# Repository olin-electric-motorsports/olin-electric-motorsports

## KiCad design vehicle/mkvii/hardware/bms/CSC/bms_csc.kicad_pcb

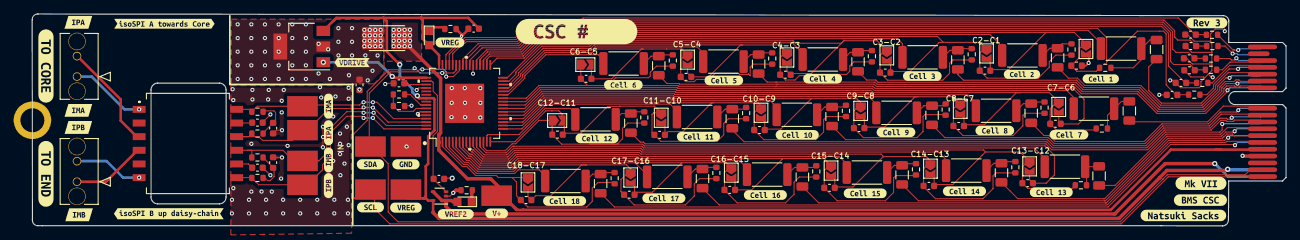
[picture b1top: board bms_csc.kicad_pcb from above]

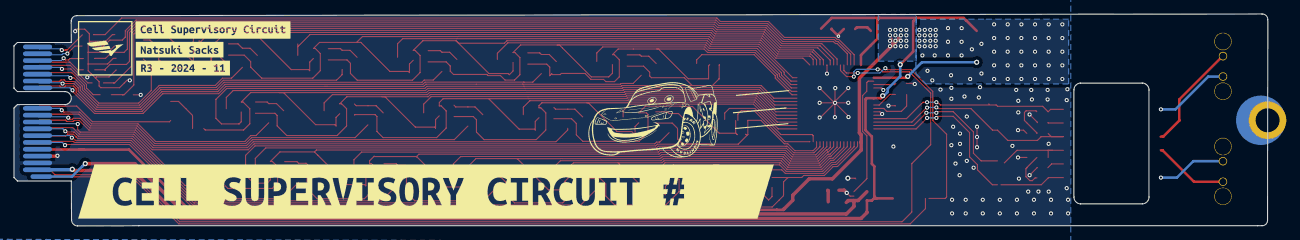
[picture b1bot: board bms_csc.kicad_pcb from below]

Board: 2 copper layers, 183.7 x 31.1 mm, 185 parts (4 on the bottom side), 110 nets.

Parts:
C1, C2, C3: C_1uF; C_0603
C4: C_0.1uF; C_0603
C5, C6, C7, C8, C9, C10, C11, C12, C13, C14, C15, C16, C17, C18, C19, C20, C21, C22, C23, C24, C25, C26, C27, C28, C29, C30, C31, C32: C_10nF; C_0603
D1, D2: LED_WHITE; CHIPLED_0805
F1, F2, F3, F4, F5, F6, F7, F8, F9, F10, F11, F12, F13, F14, F15, F16, F17, F18: 200mA_Fuse; Fuse_1206_3216Metric
H1: CONN_MountingHole; PCIe_Mount
J1, J2: 436500220; CONN_436500220
J8: CONN_pcie_x1; pcie_x1
JP1, JP2, JP3, JP4, JP5, JP6, JP7, JP8, JP9, JP10, JP11, JP12, JP13, JP14, JP15, JP16, JP17, JP18: SolderJumper_2_Open; SolderJumper-2_P1.3mm_Open_TrianglePad1.0x1.5mm
Q1: NSS1C201MZ4; SOT-223
R3: R_100; R_2512_OEM
R4, R5, R6, R7: R_60.4; R_0603
R8: 80; R_0603
R9, R10, R12, R51, R52, R53: R_100; R_0603
R11: 422; R_0603
R13, R14: R_1K; R_0603
R15, R17, R19, R21, R23, R25, R27, R29, R31, R33, R35, R37, R39, R41, R43, R45, R47, R49: 22R-1W; R_2512_6332Metric
R16, R18, R20, R22, R24, R26, R28, R30, R32, R34, R36, R38, R40, R42, R44, R46, R48, R50: 10R; R_0603
T1: HM2112ZNLT
TP1, TP2, TP3, TP4, TP19, TP20: TP_SMD; Test_Point_SMD
TP9, TP10, TP11: TP_1mm; Test_Point_SMD
U1: ADBMS1818; LQFP-64-1EP_12x12_P0.5
U2: MCP6001T-I-LT; SOT-353_SC-70-5
kibuzzard-63B4D82F: G***; kibuzzard-63B4D82F
kibuzzard-63B4D834: G***; kibuzzard-63B4D834
kibuzzard-63B4E58E: G***; kibuzzard-63B4E58E
kibuzzard-63B4E59A: G***; kibuzzard-63B4E59A
kibuzzard-63B4E581: G***; kibuzzard-63B4E581
kibuzzard-63B4E593: G***; kibuzzard-63B4E593
kibuzzard-63B4EB9B: G***; kibuzzard-63B4EB9B
kibuzzard-63B4EBA9: G***; kibuzzard-63B4EBA9
kibuzzard-63B4EBAD: G***; kibuzzard-63B4EBAD
kibuzzard-63B4EBB3: G***; kibuzzard-63B4EBB3
kibuzzard-63B4EBB8: G***; kibuzzard-63B4EBB8
kibuzzard-63B4EBF9: G***; kibuzzard-63B4EBF9
kibuzzard-63B4EC1B: G***; kibuzzard-63B4EC1B
kibuzzard-63B4EC4E: G***; kibuzzard-63B4EC4E
kibuzzard-63B4EC5B: G***; kibuzzard-63B4EC5B
kibuzzard-63B4EC6B: G***; kibuzzard-63B4EC6B
kibuzzard-63B4EC7A: G***; kibuzzard-63B4EC7A
kibuzzard-63B4EC20: G***; kibuzzard-63B4EC20
kibuzzard-63B4EC53: G***; kibuzzard-63B4EC53
kibuzzard-63B4EC66: G***; kibuzzard-63B4EC66
kibuzzard-63B4EC74: G***; kibuzzard-63B4EC74
kibuzzard-63B4EC80: G***; kibuzzard-63B4EC80
kibuzzard-63B4ED2A: G***; kibuzzard-63B4ED2A
kibuzzard-63B4ED25: G***; kibuzzard-63B4ED25
kibuzzard-63B4ED94: G***; kibuzzard-63B4ED94
kibuzzard-63BF4D5E: G***; kibuzzard-63BF4D5E
kibuzzard-672FCAF7: G***; kibuzzard-672FCAF7
kibuzzard-672FCF9D: G***; kibuzzard-672FCF9D
kibuzzard-673A717E: G***; kibuzzard-673A717E
kibuzzard-673A718C: G***; kibuzzard-673A718C
kibuzzard-673A725C: G***; kibuzzard-673A725C
kibuzzard-673A7082: G***; kibuzzard-673A7082
kibuzzard-673A7176: G***; kibuzzard-673A7176
kibuzzard-673A7184: G***; kibuzzard-673A7184
kibuzzard-673AA1F5: G***; kibuzzard-673AA1F5
kibuzzard-673AA1FB: G***; kibuzzard-673AA1FB
kibuzzard-673AA20C: G***; kibuzzard-673AA20C
kibuzzard-673AA233: G***; kibuzzard-673AA233
kibuzzard-6736A7FC: G***; kibuzzard-6736A7FC
kibuzzard-6736A805: G***; kibuzzard-6736A805
kibuzzard-6736A828: G***; kibuzzard-6736A828
kibuzzard-6736A857: G***; kibuzzard-6736A857
kibuzzard-6736A863: G***; kibuzzard-6736A863
kibuzzard-67399BB2: G***; kibuzzard-67399BB2
kibuzzard-673993C6: G***; kibuzzard-673993C6
kibuzzard-673998AC: G***; kibuzzard-673998AC
kibuzzard-6731260F: G***; kibuzzard-6731260F

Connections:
/C1: C25.2, C26.1, JP17.2 (B), JP18.1 (A), R50.2, U1.36 (C1)
/C2: C24.2, C25.1, JP16.2 (B), JP17.1 (A), R48.2, U1.34 (C2)
/C3: C23.2, C24.1, JP15.2 (B), JP16.1 (A), R46.2, U1.32 (C3)
/C4: C22.2, C23.1, JP14.2 (B), JP15.1 (A), R44.2, U1.30 (C4)
/C5: C21.2, C22.1, JP13.2 (B), JP14.1 (A), R42.2, U1.28 (C5)
/C6: C20.2, C21.1, JP12.2 (B), JP13.1 (A), R40.2, U1.26 (C6)
/C7: C19.2, C20.1, JP11.2 (B), JP12.1 (A), R38.2, U1.24 (C7)
/C8: C18.2, C19.1, JP10.2 (B), JP11.1 (A), R36.2, U1.22 (C8)
/C9: C17.2, C18.1, JP9.2 (B), JP10.1 (A), R34.2, U1.20 (C9)
/C10: C16.2, C17.1, JP8.2 (B), JP9.1 (A), R32.2, U1.18 (C10)
/C11: C15.2, C16.1, JP7.2 (B), JP8.1 (A), R30.2, U1.16 (C11)
/C12: C14.2, C15.1, JP6.2 (B), JP7.1 (A), R28.2, U1.14 (C12)
/C13: C13.2, C14.1, JP5.2 (B), JP6.1 (A), R26.2, U1.12 (C13)
/C14: C12.2, C13.1, JP4.2 (B), JP5.1 (A), R24.2, U1.10 (C14)
/C15: C9.2, C12.1, JP1.2 (B), JP4.1 (A), R22.2, U1.8 (C15)
/C16: C9.1, C11.2, JP1.1 (A), JP3.2 (B), R16.2, U1.6 (C16)
/C17: C10.2, C11.1, JP2.2 (B), JP3.1 (A), R20.2, U1.4 (C17)
/C18: C10.1, JP2.1 (A), R18.2, U1.2 (C18)
/CELL1: F18.1, J8.B14 (io_17)
/CELL2: F17.1, J8.A14 (io_16)
/CELL3: F16.1, J8.B13 (io_15)
/CELL4: F15.1, J8.A13 (io_14)
/CELL5: F14.1, J8.B12 (io_13)
/CELL6: F13.1, J8.A12 (io_12)
/CELL7: F12.1, J8.B11 (io_11)
/CELL8: F11.1, J8.A11 (io_10)
/CELL9: F10.1, J8.B10 (io_9)
/CELL10: F9.1, J8.A10 (io_8)
/CELL11: F8.1, J8.B9 (io_7)
/CELL12: F7.1, J8.A9 (io_6)
/CELL13: F6.1, J8.B8 (io_5)
/CELL14: F5.1, J8.A8 (io_4)
/CELL15: F4.1, J8.B7 (io_3)
/CELL16: F1.1, J8.A7 (io_2)
/CELL17: F3.1, J8.B6 (io_1)
/CELL18: F2.1, J8.A6 (io_0)
/IMA: R4.1, T1.12, TP2.1, U1.61 (CSBIMA)
/IMB: R6.1, T1.9, TP3.1, U1.63 (IMB)
/IPA: R5.2, T1.10, TP1.1, U1.62 (SCKIPA)
/IPB: R7.2, T1.7, TP4.1, U1.64 (IPB)
/MUX_OUT_0: J8.A15 (io_18), R9.1
/MUX_OUT_0_FILT: C27.1, R9.2, U1.39 (GPIO1)
/MUX_OUT_1: J8.B15 (io_19), R10.1
/MUX_OUT_1_FILT: C28.1, R10.2, U1.40 (GPIO2)
/MUX_OUT_2: J8.B16 (io_21), R12.1
/MUX_OUT_2_FILT: C29.1, R12.2, U1.41 (GPIO3)
/MUX_OUT_3: J8.A16 (io_20), R51.1
/MUX_OUT_3_FILT: C30.1, R51.2, U1.44 (GPIO6)
/S1: R49.2, U1.37 (S1)
/S2: R47.2, U1.35 (S2)
/S3: R45.2, U1.33 (S3)
/S4: R43.2, U1.31 (S4)
/S5: R41.2, U1.29 (S5)
/S6: R39.2, U1.27 (S6)
/S7: R37.2, U1.25 (S7)
/S8: R35.2, U1.23 (S8)
/S9: R33.2, U1.21 (S9)
/S10: R31.2, U1.19 (S10)
/S11: R29.2, U1.17 (S11)
/S12: R27.2, U1.15 (S12)
/S13: R25.2, U1.13 (S13)
/S14: R23.2, U1.11 (S14)
/S15: R21.2, U1.9 (S15)
/S16: R15.2, U1.7 (S16)
/S17: R19.2, U1.5 (S17)
/S18: R17.2, U1.3 (S18)
/SCL: J8.B1 (SCL/SCK), TP9.1, U1.43 (GPIO5)
/SDA: J8.B2 (SDA/MISO/RX), TP10.1, U1.42 (GPIO4)
/THERM_0: J8.A17 (SHDN_IN/io_22), R52.1
/THERM_0_FILT: C31.1, R52.2, U1.45 (GPIO7)
/THERM_1: J8.A18 (SHDN_IN/io_24), R53.1
/THERM_1_FILT: C32.1, R53.2, U1.46 (GPIO8)
/V+: J8.B5 (5V), R3.1, TP11.1, U1.1 (V+)
/VDRIVE: Q1.1 (B), U1.49 (VDRIVE)
/VREF2: D1.2 (A), J8.A1 (12V/3V(DA_ONLY)), U2.1, U2.4 (-)
/VREG: C3.2, D2.2 (A), J8.A2 (12V/3V(DA_ONLY)), Q1.3 (E), TP19.1, U1.48 (VREG), U1.55 (ISOMD), U2.5 (V+)
GND: C1.1, C2.1, C3.1, C4.2, C5.2, C6.2, C7.2, C8.2, C26.2, C27.2, C28.2, C29.2, C30.2, C31.2, C32.2, J8.A3 (GND), J8.B4 (GND), JP18.2 (B), R8.2, R11.2, R13.1, TP20.1, U1.38 (C0), U1.52 (DTEN), U1.59 (V-), U1.60 (V-), U1.EPAD1 (V-), U2.2 (V-)
unnamed: C4.1, Q1.2 (C), Q1.4 (C), R3.2
unnamed: C5.1, R4.2, R5.1
unnamed: C6.1, R6.2, R7.1
unnamed: C7.1, T1.11
unnamed: C8.1, T1.8
unnamed: D1.1 (K), R8.1
unnamed: D2.1 (K), R11.1
unnamed: F1.2, R15.1, R16.1
unnamed: F2.2, R17.1, R18.1
unnamed: F3.2, R19.1, R20.1
unnamed: F4.2, R21.1, R22.1
unnamed: F5.2, R23.1, R24.1
unnamed: F6.2, R25.1, R26.1
unnamed: F7.2, R27.1, R28.1
unnamed: F8.2, R29.1, R30.1
unnamed: F9.2, R31.1, R32.1
unnamed: F10.2, R33.1, R34.1
unnamed: F11.2, R35.1, R36.1
unnamed: F12.2, R37.1, R38.1
unnamed: F13.2, R39.1, R40.1
unnamed: F14.2, R41.1, R42.1
unnamed: F15.2, R43.1, R44.1
unnamed: F16.2, R45.1, R46.1
unnamed: F17.2, R47.1, R48.1
unnamed: F18.2, R49.1, R50.1
unnamed: J1.1, T1.1
unnamed: J1.2, T1.3
unnamed: J2.1, T1.4
unnamed: J2.2, T1.6
unnamed: R14.2, U1.57 (IBIAS)
unnamed: R13.2, R14.1, U1.58 (ICMP)
unnamed: C2.2, U1.51 (VREF1)
unnamed: C1.2, U1.50 (VREF2), U2.3 (+)

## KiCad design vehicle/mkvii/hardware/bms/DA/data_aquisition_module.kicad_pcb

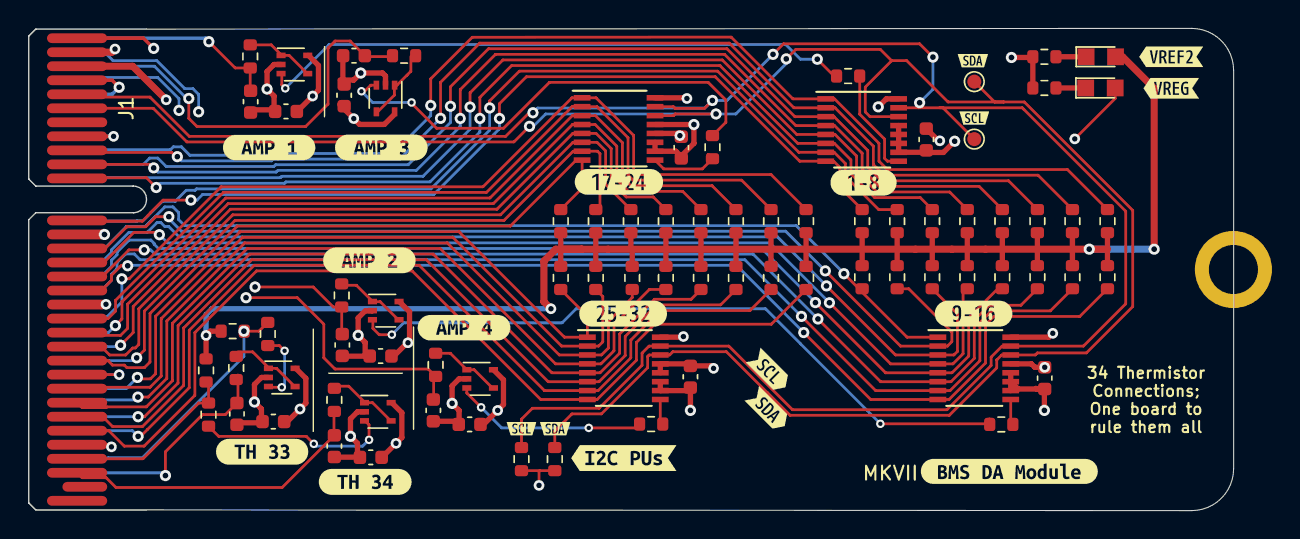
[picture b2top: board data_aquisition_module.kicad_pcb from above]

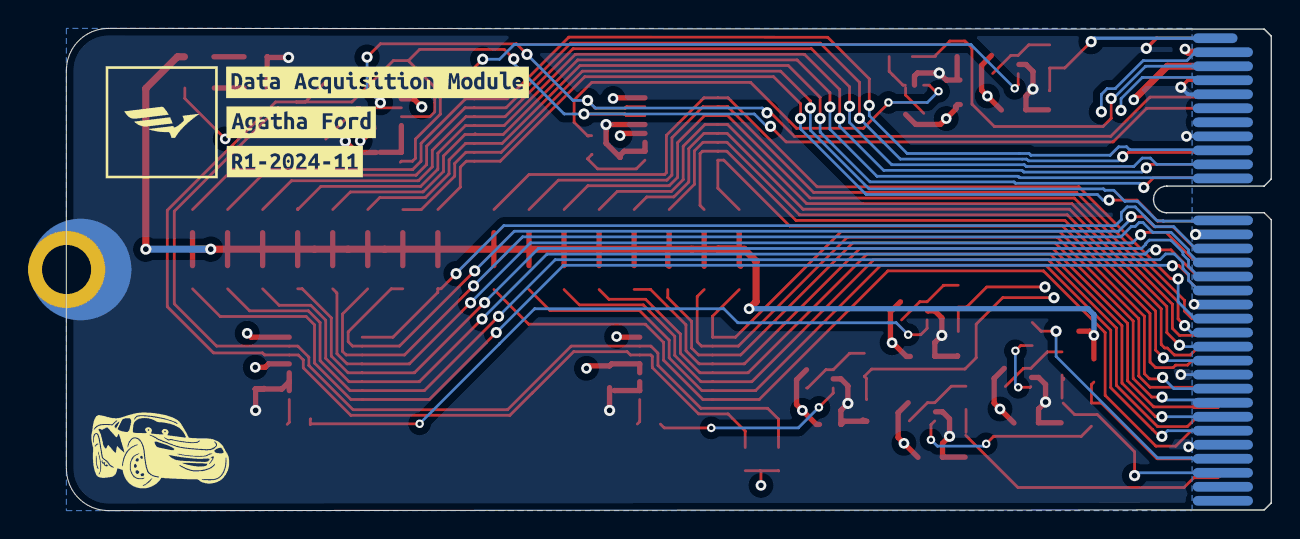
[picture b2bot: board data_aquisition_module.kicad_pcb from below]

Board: 4 copper layers, 86.0 x 34.4 mm, 105 parts (3 on the bottom side), 63 nets.

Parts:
C1, C2, C3, C4: C_1uF; C_0603
C5, C7, C9, C11, C13, C15: C_0.1uF; C_0603
C6, C8, C10, C12, C14, C16: C_10nF; C_0603
H2: CONN_MountingHole; PCIe_Mount
J1: CONN_pcie_x4; pcie_x4
PD1, PD2: WHITE; CHIPLED_0805
R1, R2, R3, R4, R5, R6, R7, R8, R9, R10, R11, R12, R13, R14, R15, R16, R17, R18, R19, R20, R21, R22, R23, R24, R25, R26, R27, R28, R29, R30, R31, R32, R45, R48: R_100K; R_0603
R33, R35, R37, R39, R41, R42, R46, R49: 1KR; R_0603
R34, R36, R38, R40, R47, R50: R_100; R_0603
R43, R44: 15KR; R_0603
TP1, TP2: TP_1mm; TestPoint_Pad_D1.0mm
U1, U2, U3, U4: LTC1380IGN; SSOP-16_3.9x4.9mm_P0.635mm
U5, U6, U7, U8, U9, U10: MCP6001T-I-LT; SOT-353_SC-70-5
kibuzzard-63A54BB0: G***; kibuzzard-63A54BB0
kibuzzard-63A54BCB: G***; kibuzzard-63A54BCB
kibuzzard-63A54BE3: G***; kibuzzard-63A54BE3
kibuzzard-63BF51CA: G***; kibuzzard-63BF51CA
kibuzzard-63BF55B8: G***; kibuzzard-63BF55B8
kibuzzard-63BF55D1: G***; kibuzzard-63BF55D1
kibuzzard-672C3C6B, kibuzzard-672C3C6B#2: G***; kibuzzard-672C3C6B
kibuzzard-672C3C52, kibuzzard-672C3C52#2: G***; kibuzzard-672C3C52
kibuzzard-672C38BF: G***; kibuzzard-672C38BF
kibuzzard-672D5DF4: G***; kibuzzard-672D5DF4
kibuzzard-673B8AB7: G***; kibuzzard-673B8AB7
kibuzzard-673B8ABD: G***; kibuzzard-673B8ABD
kibuzzard-673B8AD8: G***; kibuzzard-673B8AD8
kibuzzard-673B8ADE: G***; kibuzzard-673B8ADE
kibuzzard-673B8BCC: G***; kibuzzard-673B8BCC
kibuzzard-673B8DE4: G***; kibuzzard-673B8DE4
kibuzzard-673B8DEE: G***; kibuzzard-673B8DEE
kibuzzard-66171EA1: G***; kibuzzard-66171EA1
kibuzzard-66171EC5: G***; kibuzzard-66171EC5
kibuzzard-661723CB: G***; kibuzzard-661723CB
kibuzzard-661723F5: G***; kibuzzard-661723F5

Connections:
/MUX_1_OUT: C12.1, J1.A1 (Aout_0), R34.1
/MUX_2_OUT: C10.1, J1.A2 (Aout_1), R36.1
/MUX_3_OUT: C8.1, J1.A3 (Aout_2), R38.1
/MUX_4_OUT: C6.1, J1.A4 (Aout_3), R40.1
/SCL: J1.B5 (SCL), R43.1, TP1.1, U1.15 (SCL), U2.15 (SCL), U3.15 (SCL), U4.15 (SCL)
/SDA: J1.B6 (SDA), R44.1, TP2.1, U1.14 (SDA), U2.14 (SDA), U3.14 (SDA), U4.14 (SDA)
/THERM_1: J1.A9 (Ain_0), R1.2, U1.1 (S0)
/THERM_2: J1.B9 (Ain_1), R2.2, U1.2 (S1)
/THERM_3: J1.A10 (Ain_2), R3.2, U1.3 (S2)
/THERM_4: J1.B10 (Ain_3), R4.2, U1.4 (S3)
/THERM_5: J1.A11 (Ain_4), R5.2, U1.5 (S4)
/THERM_6: J1.B11 (Ain_5), R6.2, U1.6 (S5)
/THERM_7: J1.A12 (Ain_6), R7.2, U1.7 (S6)
/THERM_8: J1.B12 (Ain_7), R8.2, U1.8 (S7)
/THERM_9: J1.A14 (Ain_8), R9.2, U2.1 (S0)
/THERM_10: J1.B14 (Ain_9), R10.2, U2.2 (S1)
/THERM_11: J1.A15 (Ain_10), R11.2, U2.3 (S2)
/THERM_12: J1.B15 (Ain_11), R12.2, U2.4 (S3)
/THERM_13: J1.A16 (Ain_12), R13.2, U2.5 (S4)
/THERM_14: J1.B16 (Ain_13), R14.2, U2.6 (S5)
/THERM_15: J1.A17 (Ain_14), R15.2, U2.7 (S6)
/THERM_16: J1.B17 (Ain_15), R16.2, U2.8 (S7)
/THERM_17: J1.A19 (Ain_16), R17.2, U3.1 (S0)
/THERM_18: J1.B19 (Ain_17), R18.2, U3.2 (S1)
/THERM_19: J1.A20 (Ain_18), R19.2, U3.3 (S2)
/THERM_20: J1.B20 (Ain_19), R20.2, U3.4 (S3)
/THERM_21: J1.A21 (Ain_20), R21.2, U3.5 (S4)
/THERM_22: J1.B21 (Ain_21), R22.2, U3.6 (S5)
/THERM_23: J1.A22 (Ain_22), R23.2, U3.7 (S6)
/THERM_24: J1.B22 (Ain_23), R24.2, U3.8 (S7)
/THERM_25: J1.A24 (Ain_24), R25.2, U4.1 (S0)
/THERM_26: J1.B24 (Ain_25), R26.2, U4.2 (S1)
/THERM_27: J1.A25 (Ain_26), R27.2, U4.3 (S2)
/THERM_28: J1.B25 (Ain_27), R28.2, U4.4 (S3)
/THERM_29: J1.A26 (Ain_28), R29.2, U4.5 (S4)
/THERM_30: J1.B26 (Ain_29), R30.2, U4.6 (S5)
/THERM_31: J1.A27 (Ain_30), R31.2, U4.7 (S6)
/THERM_32: J1.B27 (Ain_31), R32.2, U4.8 (S7)
/THERM_33: J1.A29 (Ain_32), R45.2, R46.1
/THERM_33_OUT: C14.1, J1.A30 (Ain_34), R47.1
/THERM_34: J1.B29 (Ain_33), R48.2, R49.1
/THERM_34_OUT: C16.1, J1.B30 (Ain_35), R50.1
/VREF2: J1.B3 (3V), PD2.2 (A), R1.1, R2.1, R3.1, R4.1, R5.1, R6.1, R7.1, R8.1, R9.1, R10.1, R11.1, R12.1, R13.1, R14.1, R15.1, R16.1, R17.1, R18.1, R19.1, R20.1, R21.1, R22.1, R23.1, R24.1, R25.1, R26.1, R27.1, R28.1, R29.1, R30.1, R31.1, R32.1, R45.1, R48.1
/VREG: C1.1, C2.1, C3.1, C4.1, C5.1, C7.1, C9.1, C11.1, C13.1, C15.1, J1.B2 (5V), PD1.2 (A), R43.2, R44.2, U1.16 (VCC), U2.13 (A0), U2.16 (VCC), U3.12 (A1), U3.16 (VCC), U4.12 (A1), U4.13 (A0), U4.16 (VCC), U5.5 (V+), U6.5 (V+), U7.5 (V+), U8.5 (V+), U9.5 (V+), U10.5 (V+)
GND: C1.2, C2.2, C3.2, C4.2, C5.2, C6.2, C7.2, C8.2, C9.2, C10.2, C11.2, C12.2, C13.2, C14.2, C15.2, C16.2, H2.1, J1.A5 (GND), J1.A8 (GND), J1.A13 (GND), J1.A18 (GND), J1.A23 (GND), J1.A28 (GND), J1.B1 (GND), J1.B4 (GND), J1.B8 (GND), J1.B13 (GND), J1.B18 (GND), J1.B23 (GND), J1.B28 (GND), R41.2, R42.2, U1.10 (VEE), U1.11 (GND), U1.12 (A1), U1.13 (A0), U2.10 (VEE), U2.11 (GND), U2.12 (A1), U3.10 (VEE), U3.11 (GND), U3.13 (A0), U4.10 (VEE), U4.11 (GND), U5.2 (V-), U6.2 (V-), U7.2 (V-), U8.2 (V-), U9.2 (V-), U10.2 (V-)
unnamed: PD1.1 (K), R41.1
unnamed: PD2.1 (K), R42.1
unnamed: R33.1, U1.9 (D0)
unnamed: R35.1, U2.9 (D0)
unnamed: R37.1, U3.9 (D0)
unnamed: R39.1, U4.9 (D0)
unnamed: R39.2, U5.3 (+)
unnamed: R40.2, U5.1, U5.4 (-)
unnamed: R37.2, U6.3 (+)
unnamed: R38.2, U6.1, U6.4 (-)
unnamed: R35.2, U7.3 (+)
unnamed: R36.2, U7.1, U7.4 (-)
unnamed: R33.2, U8.3 (+)
unnamed: R34.2, U8.1, U8.4 (-)
unnamed: R46.2, U9.3 (+)
unnamed: R47.2, U9.1, U9.4 (-)
unnamed: R49.2, U10.3 (+)
unnamed: R50.2, U10.1, U10.4 (-)

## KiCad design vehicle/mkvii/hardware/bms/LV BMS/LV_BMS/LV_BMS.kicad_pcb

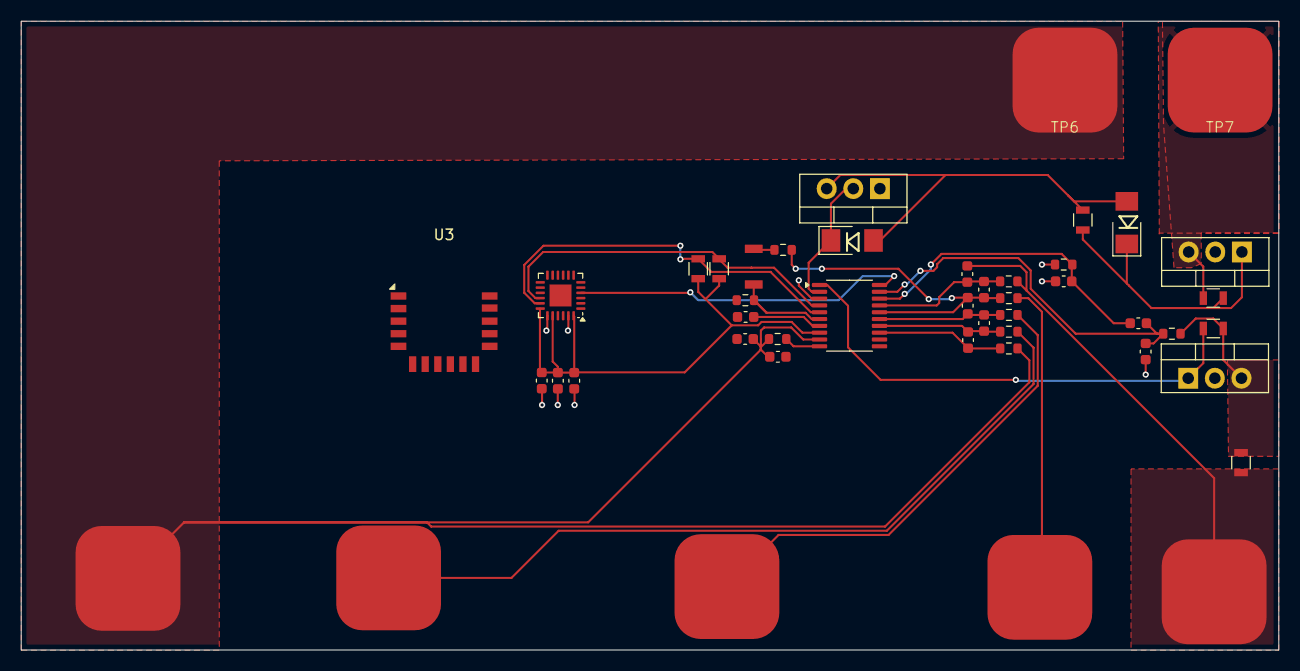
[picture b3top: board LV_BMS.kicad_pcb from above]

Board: 2 copper layers, 120.0 x 60.0 mm, 46 parts (0 on the bottom side), 29 nets.

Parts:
C1, C2, C4, C5, C6, C7, C8: C_1uF; C_0603
C3: C_10uF; C_0603
C9, C10, C11, C12, C13, C14: C_0.1uF; C_0603
D1, D2: D_Schottky_KA_template; DO-214AA
Q1, Q2: IRF3205; TO-220-3_Vertical
Q3: IRF9540N; TO-220-3_Vertical
R1, R2, R3, R4, R5, R6, R7, R8: R_100; R_0603
R9, R10, R11: R_1M; R_0805_OEM
R12, R13: R_4.7K; R_0805_OEM
R14: R_10K; R_0603
Rsns1: R; R_0805_OEM
SW1: SW_Push_SPST_NO; SW_B3U-1000P_4.2x1.7mm
TH1: R_Thermistor_10K; R_0603
TP1, TP2, TP3, TP4, TP5, TP6, TP7: TestPoint; 4sPad
U1: BQ76920PW; TSSOP-20_4.4x6.5mm_P0.65mm
U2: MSP430FR5738IRGE; Texas_RGE0024C_VQFN-24-1EP_4x4mm_P0.5mm_EP2.1x2.1mm
U3: RN4871; Microchip_RN4871

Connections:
/ALERT: U1.20 (ALERT), U2.4 (TA1.2/UCB0STE/CD3/A3/P1.3)
/B1: C5.1, C6.1, R3.2, R14.1, U1.16 (VC1)
/B2: C6.2, C7.1, R4.2, U1.15 (VC2)
/B3: C7.2, C8.1, R5.2, U1.14 (VC3)
/B+: C8.2, R6.2, U1.13 (VC4)
/B+(unf): C1.2, C3.1, R1.2, R6.1, TP5.1, TP6.1, U1.9 (REGSRC)
/C-: Q2.3 (S), R10.1, TP7.1
/CHG: D1.1 (K), D2.1 (K), Q2.1 (G), Q3.2 (D), R10.2, R11.2, U1.2 (CHG)
/DSG: Q1.1 (G), R9.2, U1.1 (DSG)
/MOSIN: Q1.3 (S), R8.1, R9.1, Rsns1.1
/MOSINT: Q1.2 (D), Q2.2 (D)
/RESET: U2.5 (TB0.1/UCA0STE/CD4/A4/P1.4), U3.10 (RST)
/RX: U2.2 (TA0.2/TA1CLK/CDOUT/CD1/VeREF+/A1/P1.1), U3.7 (UART_RX)
/SCL: R13.1, U1.5 (SCL), U2.17 (TA1.0/UCB0SOMI/UCB0SCL/P1.7)
/SDA: R12.1, U1.4 (SDA), U2.16 (TA0.0/UCB0SIMO/UCB0SDA/P1.6)
/SRN: C9.2, C11.1, R8.2, U1.19 (SRN)
/SRP: C9.1, C10.2, R7.1, U1.18 (SRP)
/TX: U2.3 (TA1.1/TA0CLK/CDOUT/CD2/A2/P1.2), U3.8 (UART_TX)
/VREG: C12.1, C13.1, C14.1, R12.2, R13.2, U1.8 (REGOUT), U2.18 (VCORE), U2.20 (DVCC), U2.24 (AVCC), U3.14 (VBAT)
/WAKE: U2.6 (TB0.2/UCA0CLK/CD5/A5/P1.5), U3.4 (P1_3)
GND: C1.1, C2.1, C3.2, C4.1, C4.2, C5.2, C10.1, C11.2, C12.2, C13.2, C14.2, Q3.1 (G), R2.1, R2.2, R7.2, Rsns1.2, TH1.1, TP1.1, U1.3 (VSS), U1.17 (VC0), U2.19 (DVSS), U2.23 (AVSS), U3.2 (GND), U3.13 (GND)
unnamed: D1.2 (A), D2.2 (A), Q3.3 (S), R11.1
unnamed: R3.1, TP2.1
unnamed: R4.1, TP3.1
unnamed: R5.1, TP4.1
unnamed: R14.2, SW1.1
unnamed: R1.1, U1.10 (BAT)
unnamed: C2.2, U1.7 (CAP1)
unnamed: SW1.2, TH1.2, U1.6 (TS1)

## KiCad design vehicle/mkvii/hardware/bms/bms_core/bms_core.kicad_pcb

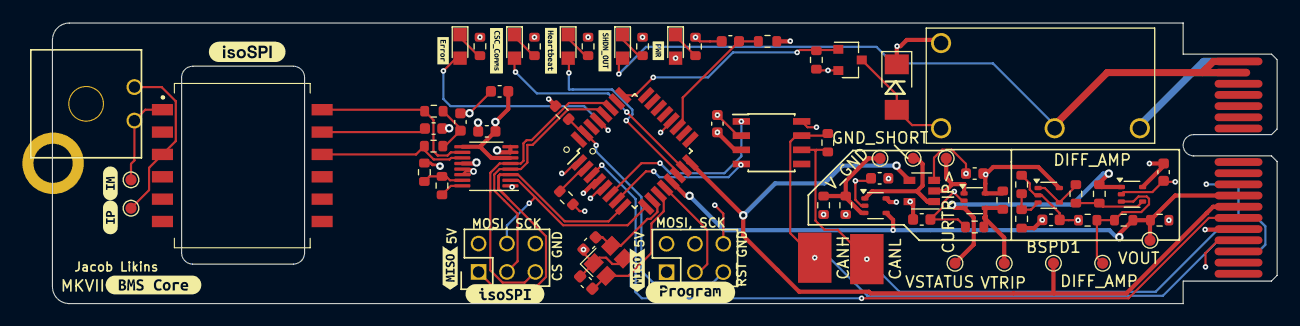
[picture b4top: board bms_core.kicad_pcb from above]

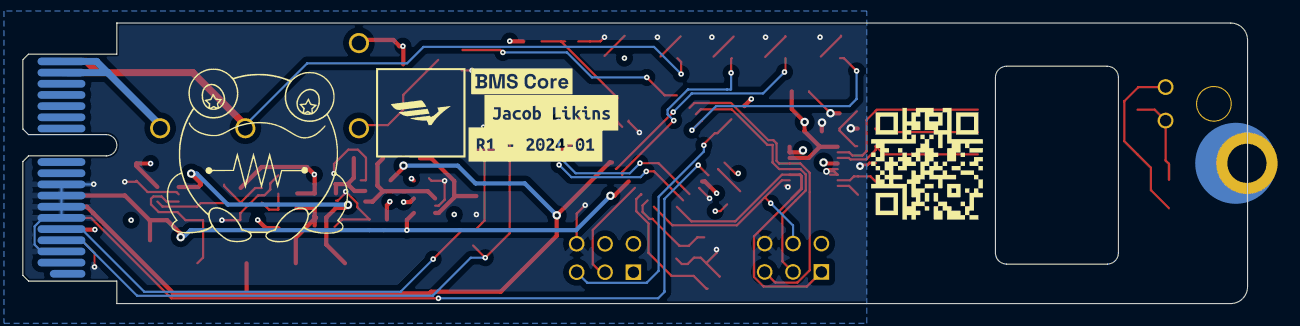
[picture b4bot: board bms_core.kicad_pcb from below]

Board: 4 copper layers, 109.6 x 25.1 mm, 90 parts (4 on the bottom side), 50 nets.

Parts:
BSPD1: BSPD_CURRENT_THRESH; TestPoint_Pad_D1.0mm
C1, C4, C6, C9, C10, C11, C12, C13: C_0.1uF; C_0603
C2: C_100pF; C_0603
C3, C5: C_30pF; C_0603
C7, C8: C_10nF; C_0603
CANH: CANH1; Test_Point_SMD
CANL: CANL1; Test_Point_SMD
CURTRIP>: CURRENT_TRIP; TestPoint_Pad_D1.0mm
D1: LED_AMBER; CHIPLED_0805
D2: LED_GREEN; CHIPLED_0805
D3: LED_RED; CHIPLED_0805
D4: LED_WHITE; CHIPLED_0805
D5: D_Zener_18V_SMBJ5355B-TP; DO-214AA
D6: LED_BLUE; CHIPLED_0805
DIFF_AMP: TP_1mm; TestPoint_Pad_D1.0mm
GND_SHORT: GND_SHORT; TestPoint_Pad_D1.0mm
H2: CONN_MountingHole; PCIe_Mount
IM1: TP_1mm; TestPoint_Pad_D1.0mm
IP1: TP_1mm; TestPoint_Pad_D1.0mm
J1, J2: CONN_02x03; Pin_Header_Straight_2x03
J3: MicroFit_RA_2
J5: CONN_pcie_x1; pcie_x1
K1: Relay_G5Q-1A4-DC5; Relay_SPST_OMRON-G5Q-1A4_OEM
Q1: SSM3K333R; SOT-23F
QR*****: hw.oem.to/QR_6_BMS-CORE_1; QR_6_BMS-CORE_1
R1, R3, R21, R22, R23: 1KR; R_0603
R2: R_100; R_0603
R4: 100R; R_0603
R5: R_120_DNP; R_0603
R6, R7, R12, R13, R14, R15, R16, R19, R24, R25: R_10K; R_0603
R8, R9, R18: R_1K; R_0603
R10, R11: R_60.4; R_0603
R17: R_1M; R_0603
R20: R_576; R_0603
T1: HM2112ZNLT
U1: ATMEGA64M1; TQFP-32_7x7mm_Pitch0.8mm
U2: MAX33011EASA; SOIC-8_3.9x4.9mm_Pitch1.27mm_OEM
U3: LTC6820HMS; MSOP-16_3x4mm_P0.5mm
U4, U5, U6, U8: MCP6001; SOT-353_SC-70-5
U7: SN74LVC1G32DBVR; SOT-23-5_OEM
VOUT: VOUT; TestPoint_Pad_D1.0mm
VSTATUS: VSTATUS; TestPoint_Pad_D1.0mm
VTRIP: VTRIP; TestPoint_Pad_D1.0mm
V_GND: V_GND_THRESHOLD; TestPoint_Pad_D1.0mm
Y1: Crystal_16MHz_18pF; Crystal_SMD_FA238
kibuzzard-63B930AD, kibuzzard-63B930AD#2: G***; kibuzzard-63B930AD
kibuzzard-63B9305B: G***; kibuzzard-63B9305B
kibuzzard-63B93076: G***; kibuzzard-63B93076
kibuzzard-63BB8A3F: G***; kibuzzard-63BB8A3F
kibuzzard-63BB8A53: G***; kibuzzard-63BB8A53
kibuzzard-63BF4A21: G***; kibuzzard-63BF4A21
kibuzzard-63BF43E2: G***; kibuzzard-63BF43E2
kibuzzard-63BF57C4: G***; kibuzzard-63BF57C4
kibuzzard-671D4F66: G***; kibuzzard-671D4F66
kibuzzard-671D5265: G***; kibuzzard-671D5265
kibuzzard-671D5273: G***; kibuzzard-671D5273
kibuzzard-671D5279: G***; kibuzzard-671D5279
kibuzzard-671FF51F: G***; kibuzzard-671FF51F
kibuzzard-67240C9D: G***; kibuzzard-67240C9D
kibuzzard-67240CB0: G***; kibuzzard-67240CB0

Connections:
+5V: C1.1, C4.1, C6.1, C9.1, C10.1, C11.1, C12.1, C13.1, D4.2 (A), D5.1 (K), J1.2, J2.2, J5.B5 (5V), K1.5, R2.1, R6.1, R12.2, R17.1, R19.2, R24.1, U1.4 (VCC), U2.3 (VDD), U3.6 (VDDS), U3.7 (POL), U3.8 (PHA), U3.9 (VDD), U3.12 (MSTR), U4.5 (V+), U5.5 (V+), U6.5 (V+), U7.5 (VCC), U8.5 (V+)
/BMS_RELAY_DRIVE: Q1.1 (G), R7.2, U1.25 ((PCINT15/D2A/AMP2+)PC7)
/BSPD Current Sensor Trigger/CURRENT_TRIP: CURTRIP>.1, U6.1, U7.2 (in)
/BSPD Current Sensor Trigger/GND_SHORT: GND_SHORT.1, U5.1, U7.1 (in)
/BSPD Current Sensor Trigger/VSTATUS: R15.2, U4.1, U6.3 (+), VSTATUS.1
/BSPD Current Sensor Trigger/VTRIP: R19.1, R20.1, U6.4 (-), VTRIP.1
/BSPD Current Sensor Trigger/V_GND_THRESHOLD: R17.2, R18.1, U5.3 (+), V_GND.1
/BSPD_CURRENT_THRESH: BSPD1.1, J5.B7 (io_3), U1.16 ((PCINT2/ADC5/INT1/ACMPN0)PB2), U7.4 (out)
/CANH: CANH.1, J5.A4 (CAN+), R5.1, U2.7 (CANH)
/CANL: CANL.1, J5.A5 (CAN-), R5.2, U2.6 (CANL)
/CSC_Comms: D2.2 (A), U1.15 ((PCINT23/ACMP0)PD7)
/Error: D3.2 (A), U1.29 ((PCINT16/PSCOUT0A)PD0)
/FAN_PWM: J5.B6 (io_1), U1.3 ((PCINT9/PSCIN1/OC1B/~SS_A)PC1)
/Heartbeat: D1.2 (A), U1.14 ((PCINT22/ADC3/INT0/ACMPN2)PD6)
/IM: IM1.1, J3.1, T1.1
/IP: IP1.1, J3.2, T1.3
/ISO_CS: J2.5, U1.27 ((PCINT6/ADC7/PSCOUT1B)PB6), U3.5 (~CS)
/ISO_MISO: J2.1, U1.8 ((PCINT0/MISO/PSCOUT2A)PB0), U3.3 (MISO)
/ISO_MOSI: J2.4, U1.9 ((PCINT1/MOSI/PSCOUT2B)PB1), U3.2 (MOSI)
/ISO_SCK: J2.3, U1.28 ((PCINT7/ADC4/SCK/PSCOUT0B)PB7), U3.4 (SCK)
/MISO: J1.1, U1.1 ((PCINT18/PSCIN2/OC1A/MISO_A)PD2)
/MOSI: J1.4, R4.1
/RESET: J1.5, R6.2, U1.31 ((PCINT24/OCD/~RESET)PE0)
/RXCAN: U1.7 ((PCINT11/T1/ICP1B/RXCAN)PC3), U2.4 (RXD)
/SCK: J1.3, U1.12 ((PCINT20/ADC1/RXD/RXLIN/ICP1A/SCK_A)PD4)
/SHDN_IN: J5.A17 (SHDN_IN/io_22), J5.A18 (SHDN_IN/io_24), K1.3
/SHDN_OUT: D6.2 (A), J5.B17 (SHDN_OUT/io_23), J5.B18 (SHDN_OUT/io_25), K1.2
/TXCAN: U1.6 ((PCINT10/T0/TXCAN)PC2), U2.1 (TXD)
/VOUT_CURRENT_SENSE: J5.B8 (io_5), R12.1, R13.1, U1.13 ((PCINT21/ADC2/ACMP2)PD5), U5.4 (-), VOUT.1
GND: C1.2, C2.2, C3.2, C4.2, C5.2, C6.2, C7.2, C8.2, C9.2, C10.2, C11.2, C12.2, C13.2, J1.6, J2.6, J5.A3 (GND), J5.A6 (io_0), J5.A7 (io_2), J5.A8 (io_4), J5.A9 (io_6), J5.B4 (GND), Q1.2 (S), R1.2, R3.2, R7.1, R9.2, R14.1, R18.2, R20.2, R21.2, R22.2, R23.2, R25.2, U1.5 (GND), U1.20 (AGND), U2.2 (VSS), U2.8 (STBY), U3.1 (EN), U3.13 (SLOW), U3.14 (GND), U4.2 (V-), U5.2 (V-), U6.2 (V-), U7.3 (GND), U8.2 (V-), Y1.2, Y1.4
unnamed: C7.1, R10.2, R11.1
unnamed: C8.1, T1.11
unnamed: D1.1 (K), R1.1
unnamed: D2.1 (K), R3.1
unnamed: D3.1 (K), R21.1
unnamed: D4.1 (K), R22.1
unnamed: D5.2 (A), K1.1, Q1.3 (D)
unnamed: D6.1 (K), R23.1
unnamed: R4.2, U1.2 ((PCINT19/TXD/TXLIN/OC0A/~SS/MOSI_A)PD3)
unnamed: C5.1, U1.10 ((PCINT25/OC0B/XTAL1)PE1), Y1.3
unnamed: C3.1, U1.11 ((PCINT26/ADC0/XTAL2)PE2), Y1.1
unnamed: C2.1, R2.2, U1.19 (AVCC)
unnamed: R8.1, U3.16 (IBIAS)
unnamed: R8.2, R9.1, U3.15 (ICMP)
unnamed: R10.1, T1.12, U3.10 (IM)
unnamed: R11.2, T1.10, U3.11 (IP)
unnamed: DIFF_AMP.1, R13.2, R14.2, U4.3 (+)
unnamed: R15.1, R16.2, U4.4 (-)
unnamed: R24.2, R25.1, U8.3 (+)
unnamed: R16.1, U8.1, U8.4 (-)

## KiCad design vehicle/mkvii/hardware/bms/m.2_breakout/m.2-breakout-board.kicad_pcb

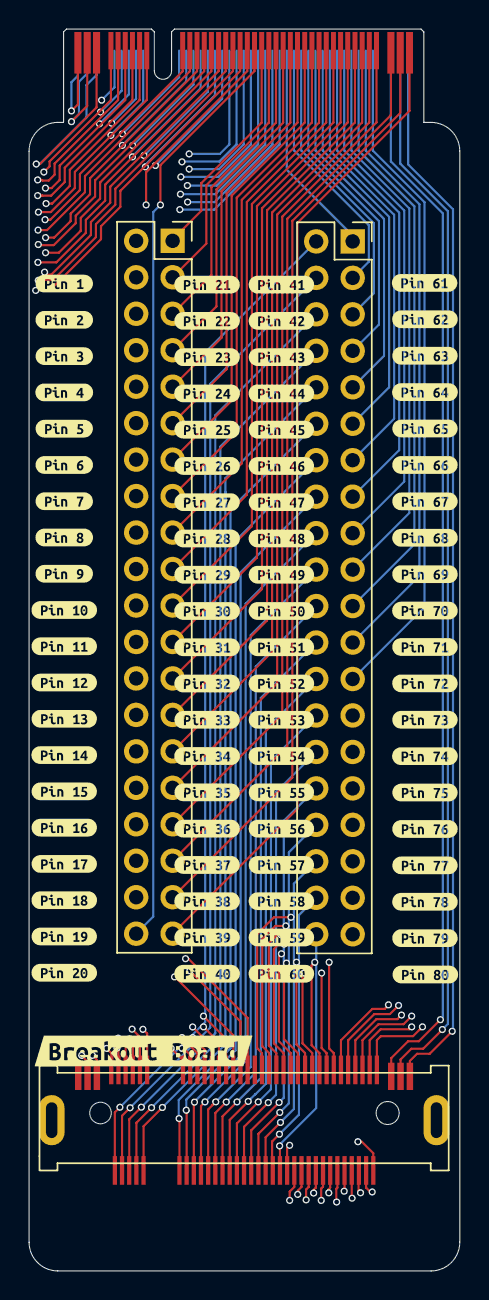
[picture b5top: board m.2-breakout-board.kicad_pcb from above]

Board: 4 copper layers, 30.0 x 86.5 mm, 85 parts (0 on the bottom side), 73 nets.

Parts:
J1: Pin_Header_1; PinSocket_2x20_P2.54mm_Vertical
J2: Pin_Header_2; PinSocket_2x20_P2.54mm_Vertical
J3: Automotive_M.2_Edge_Connector
J4: Automotive_M.2
kibuzzard-65E4F8A3: G***; kibuzzard-65E4F8A3
kibuzzard-65E4F8A7: G***; kibuzzard-65E4F8A7
kibuzzard-65E4F8AD: G***; kibuzzard-65E4F8AD
kibuzzard-65E4F9A4: G***; kibuzzard-65E4F9A4
kibuzzard-65E4F9A9: G***; kibuzzard-65E4F9A9
kibuzzard-65E4F9B0: G***; kibuzzard-65E4F9B0
kibuzzard-65E4F9B6: G***; kibuzzard-65E4F9B6
kibuzzard-65E4F9CB: G***; kibuzzard-65E4F9CB
kibuzzard-65E4F9F7: G***; kibuzzard-65E4F9F7
kibuzzard-65E4F9FC: G***; kibuzzard-65E4F9FC
kibuzzard-65E4F90C: G***; kibuzzard-65E4F90C
kibuzzard-65E4F92D: G***; kibuzzard-65E4F92D
kibuzzard-65E4F93A: G***; kibuzzard-65E4F93A
kibuzzard-65E4F94A: G***; kibuzzard-65E4F94A
kibuzzard-65E4F95B: G***; kibuzzard-65E4F95B
kibuzzard-65E4F96C: G***; kibuzzard-65E4F96C
kibuzzard-65E4F97B: G***; kibuzzard-65E4F97B
kibuzzard-65E4F98D: G***; kibuzzard-65E4F98D
kibuzzard-65E4F99B: G***; kibuzzard-65E4F99B
kibuzzard-65E4F907: G***; kibuzzard-65E4F907
kibuzzard-65E4F911: G***; kibuzzard-65E4F911
kibuzzard-65E4F916: G***; kibuzzard-65E4F916
kibuzzard-65E4F928: G***; kibuzzard-65E4F928
kibuzzard-65E4F932: G***; kibuzzard-65E4F932
kibuzzard-65E4F936: G***; kibuzzard-65E4F936
kibuzzard-65E4F941: G***; kibuzzard-65E4F941
kibuzzard-65E4F946: G***; kibuzzard-65E4F946
kibuzzard-65E4F951: G***; kibuzzard-65E4F951
kibuzzard-65E4F955: G***; kibuzzard-65E4F955
kibuzzard-65E4F960: G***; kibuzzard-65E4F960
kibuzzard-65E4F981: G***; kibuzzard-65E4F981
kibuzzard-65E4F987: G***; kibuzzard-65E4F987
kibuzzard-65E4F991: G***; kibuzzard-65E4F991
kibuzzard-65E4F997: G***; kibuzzard-65E4F997
kibuzzard-65E4FA07: G***; kibuzzard-65E4FA07
kibuzzard-65E4FB5F: G***; kibuzzard-65E4FB5F
kibuzzard-65E4FB6A: G***; kibuzzard-65E4FB6A
kibuzzard-65E4FB7A: G***; kibuzzard-65E4FB7A
kibuzzard-65E4FB72: G***; kibuzzard-65E4FB72
kibuzzard-65E4FB85: G***; kibuzzard-65E4FB85
kibuzzard-65E4FB98: G***; kibuzzard-65E4FB98
kibuzzard-65E4FBA6: G***; kibuzzard-65E4FBA6
kibuzzard-65E4FBAD: G***; kibuzzard-65E4FBAD
kibuzzard-65E4FBB5: G***; kibuzzard-65E4FBB5
kibuzzard-65E4FBBB: G***; kibuzzard-65E4FBBB
kibuzzard-65E4FBCB: G***; kibuzzard-65E4FBCB
kibuzzard-65E4FBD4: G***; kibuzzard-65E4FBD4
kibuzzard-65E4FBDC: G***; kibuzzard-65E4FBDC
kibuzzard-65E4FBE5: G***; kibuzzard-65E4FBE5
kibuzzard-65E4FBEC: G***; kibuzzard-65E4FBEC
kibuzzard-65E4FBF3: G***; kibuzzard-65E4FBF3
kibuzzard-65E4FC00: G***; kibuzzard-65E4FC00
kibuzzard-65E4FC1B: G***; kibuzzard-65E4FC1B
kibuzzard-65E4FC2C: G***; kibuzzard-65E4FC2C
kibuzzard-65E4FC5A: G***; kibuzzard-65E4FC5A
kibuzzard-65E4FC6E: G***; kibuzzard-65E4FC6E
kibuzzard-65E4FC7A: G***; kibuzzard-65E4FC7A
kibuzzard-65E4FC7E: G***; kibuzzard-65E4FC7E
kibuzzard-65E4FC08: G***; kibuzzard-65E4FC08
kibuzzard-65E4FC8B: G***; kibuzzard-65E4FC8B
kibuzzard-65E4FC8F: G***; kibuzzard-65E4FC8F
kibuzzard-65E4FC9A: G***; kibuzzard-65E4FC9A
kibuzzard-65E4FC9E: G***; kibuzzard-65E4FC9E
kibuzzard-65E4FC24: G***; kibuzzard-65E4FC24
kibuzzard-65E4FC33: G***; kibuzzard-65E4FC33
kibuzzard-65E4FC39: G***; kibuzzard-65E4FC39
kibuzzard-65E4FC40: G***; kibuzzard-65E4FC40
kibuzzard-65E4FC47: G***; kibuzzard-65E4FC47
kibuzzard-65E4FC55: G***; kibuzzard-65E4FC55
kibuzzard-65E4FC61: G***; kibuzzard-65E4FC61
kibuzzard-65E4FC65: G***; kibuzzard-65E4FC65
kibuzzard-65E4FC69: G***; kibuzzard-65E4FC69
kibuzzard-65E4FC72: G***; kibuzzard-65E4FC72
kibuzzard-65E4FC83: G***; kibuzzard-65E4FC83
kibuzzard-65E4FC86: G***; kibuzzard-65E4FC86
kibuzzard-65E4FC95: G***; kibuzzard-65E4FC95
kibuzzard-65E4FCA3: G***; kibuzzard-65E4FCA3
kibuzzard-65E4FCA8: G***; kibuzzard-65E4FCA8
kibuzzard-65E4FCAC: G***; kibuzzard-65E4FCAC
kibuzzard-65E4FCB0: G***; kibuzzard-65E4FCB0
kibuzzard-65E52195: G***; kibuzzard-65E52195

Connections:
/1: J1.1, J3.P1, J4.P1
/2: J1.2, J3.P2, J4.P2
/3: J1.3, J3.P3, J4.P3
/4: J1.4, J3.4, J4.4
/5: J1.5, J3.5, J4.5
/6: J1.6, J3.6, J4.6
/7: J1.7, J3.7, J4.7
/8: J1.8, J3.8, J4.8
/9: J1.9, J3.9, J4.9
/10: J1.10, J3.10, J4.10
/11: J1.11, J3.11, J4.11
/12: J1.12, J3.12, J4.12
/13: J1.13, J3.13, J4.13
/14: J1.14, J3.14, J4.14
/15: J1.15, J3.15, J4.15
/16: J1.16, J3.16, J4.16
/17: J1.17, J3.17, J4.17
/18: J1.18, J3.18, J4.18
/19: J1.19, J3.19, J4.19
/20: J1.20, J3.20, J4.20
/21: J1.21, J3.21, J4.21
/22: J1.22, J3.22, J4.22
/23: J1.23, J3.23, J4.23
/24: J1.24, J3.24, J4.24
/25: J1.25, J3.25, J4.25
/26: J1.26, J3.26, J4.26
/27: J1.27, J3.27, J4.27
/28: J1.28, J3.28, J4.28
/29: J1.29, J3.29, J4.29
/30: J1.30, J3.30, J4.30
/31: J1.31, J3.31, J4.31
/32: J1.32, J3.32, J4.32
/33: J1.33, J3.33, J4.33
/34: J1.34, J3.34, J4.34
/35: J1.35, J3.35, J4.35
/36: J1.36, J3.36, J4.36
/37: J1.37, J3.37, J4.37
/38: J1.38, J3.P38, J4.P38
/39: J1.39, J3.P39, J4.P39
/40: J1.40, J3.P40, J4.P40
/41: J2.41, J3.41, J4.41
/42: J2.42, J3.42, J4.42
/43: J2.43, J3.43, J4.43
/44: J2.44, J3.44, J4.44
/45: J2.45, J3.45, J4.45
/46: J2.46, J3.46, J4.46
/47: J2.47, J3.47, J4.47
/48: J2.48, J3.48, J4.48
/49: J2.49, J3.49, J4.49
/50: J2.50, J3.50, J4.50
/51: J2.51, J3.51, J4.51
/52: J2.52, J3.52, J4.52
/53: J2.53, J3.53, J4.53
/54: J2.54, J3.54, J4.54
/55: J2.55, J3.55, J4.55
/56: J2.56, J3.56, J4.56
/57: J2.57, J3.57, J4.57
/58: J2.58, J3.58, J4.58
/59: J2.59, J3.59, J4.59
/60: J2.60, J3.60, J4.60
/61: J2.61 (Pin_1), J3.61, J4.61
/62: J2.62 (Pin_3), J3.62, J4.62
/63: J2.63 (Pin_5), J3.63, J4.63
/64: J2.64 (Pin_7), J3.64, J4.64
/65: J2.65 (Pin_9), J3.65, J4.65
/66: J2.66 (Pin_11), J3.66, J4.66
/67: J2.67 (Pin_13), J3.67, J4.67
/68: J2.68 (Pin_15), J3.68, J4.68
/69: J2.69 (Pin_17), J3.69, J4.69
/70: J2.70 (Pin_19), J3.70, J4.70
/71: J2.71 (Pin_21), J3.71, J4.71
/72: J2.72 (Pin_23), J3.72, J4.72
/73: J2.73 (Pin_25), J3.73, J4.73

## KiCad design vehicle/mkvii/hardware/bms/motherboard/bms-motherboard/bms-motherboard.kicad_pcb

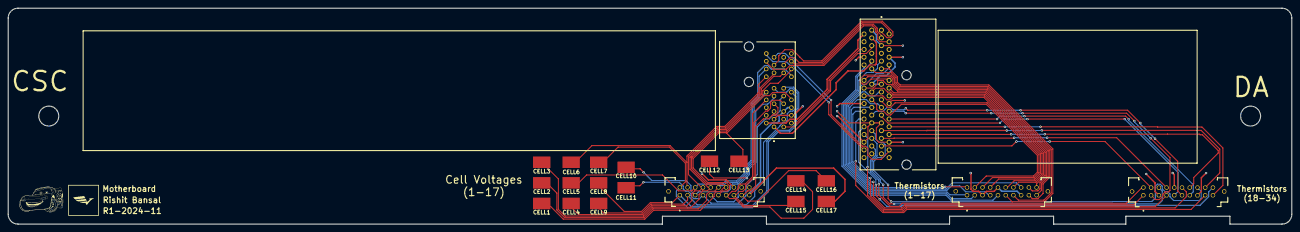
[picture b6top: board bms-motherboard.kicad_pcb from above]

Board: 2 copper layers, 332.2 x 55.9 mm, 22 parts (0 on the bottom side), 62 nets.

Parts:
CELL1, CELL2, CELL3, CELL4, CELL5, CELL6, CELL7, CELL8, CELL9, CELL10, CELL11, CELL12, CELL14, CELL15, CELL16, CELL17: TP_SMD; Test_Point_SMD
J1, J2, J3: T2M-110-01-X-D-TH-WT; SAMTEC_T2M-110-01-X-D-TH-WT
J4: CONN_pcie_x1; te_pcie_x1_connector
J5: CONN_pcie_x4; te_pcie_x4_connector
TP4: TP_SMD; Test_Point_SMD

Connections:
/MUX_OUT_1: J4.A15 (io_18), J5.A1 (Aout_0)
/MUX_OUT_2: J4.B15 (io_19), J5.A2 (Aout_1)
/MUX_OUT_3: J4.B16 (io_21), J5.A3 (Aout_2)
/MUX_OUT_4: J4.A16 (io_20), J5.A4 (Aout_3)
/SCL: J4.B1 (SCL/SCK), J5.B5 (SCL)
/SDA: J4.B2 (SDA/MISO/RX), J5.B6 (SDA)
/THERM_33_OUT: J4.A17 (SHDN_IN/io_22), J5.A30 (Ain_34)
/THERM_34_OUT: J4.A18 (SHDN_IN/io_24), J5.B30 (Ain_35)
/VREF2: J4.A1 (12V/3V(DA_ONLY)), J5.B3 (3V)
/VREG: J4.A2 (12V/3V(DA_ONLY)), J5.B2 (5V)
CELL1: CELL1.1, J1.14, J4.B14 (io_17)
CELL2: CELL2.1, J1.12, J4.A14 (io_16)
CELL3: CELL3.1, J1.10, J4.B13 (io_15)
CELL4: CELL4.1, J1.08, J4.A13 (io_14)
CELL5: CELL5.1, J1.06, J4.B12 (io_13)
CELL6: CELL6.1, J1.04, J4.A12 (io_12)
CELL7: CELL7.1, J1.02, J4.B11 (io_11)
CELL8: CELL8.1, J1.01, J4.A11 (io_10)
CELL9: CELL9.1, J1.03, J4.B10 (io_9)
CELL10: CELL10.1, J1.05, J4.A10 (io_8)
CELL11: CELL11.1, J1.07, J4.B9 (io_7)
CELL12: CELL12.1, J1.09, J4.A9 (io_6)
CELL13: J1.11, J4.B8 (io_5), TP4.1
CELL14: CELL14.1, J1.13, J4.A8 (io_4)
CELL15: CELL15.1, J1.15, J4.B7 (io_3)
CELL16: CELL16.1, J1.17, J4.A7 (io_2)
CELL17: CELL17.1, J1.19, J4.B5 (5V), J4.B6 (io_1)
GND: J1.16, J2.05, J2.10, J2.15, J3.05, J3.10, J3.15, J4.A3 (GND), J4.B4 (GND), J5.A5 (GND), J5.A8 (GND), J5.A13 (GND), J5.A18 (GND), J5.A23 (GND), J5.A28 (GND), J5.B1 (GND), J5.B4 (GND), J5.B8 (GND), J5.B13 (GND), J5.B18 (GND), J5.B23 (GND), J5.B28 (GND)
THERM1: J3.01, J5.A9 (Ain_0)
THERM2: J3.03, J5.B9 (Ain_1)
THERM3: J3.07, J5.A10 (Ain_2)
THERM4: J3.09, J5.B10 (Ain_3)
THERM5: J3.11, J5.A11 (Ain_4)
THERM6: J3.13, J5.B11 (Ain_5)
THERM7: J3.17, J5.A12 (Ain_6)
THERM8: J3.19, J5.B12 (Ain_7)
THERM9: J3.20, J5.A14 (Ain_8)
THERM10: J3.18, J5.B14 (Ain_9)
THERM11: J3.16, J5.A15 (Ain_10)
THERM12: J3.14, J5.B15 (Ain_11)
THERM13: J3.12, J5.A16 (Ain_12)
THERM14: J3.08, J5.B16 (Ain_13)
THERM15: J3.06, J5.A17 (Ain_14)
THERM16: J3.04, J5.B17 (Ain_15)
THERM17: J3.02, J5.A19 (Ain_16)
THERM18: J2.01, J5.B19 (Ain_17)
THERM19: J2.03, J5.A20 (Ain_18)
THERM20: J2.07, J5.B20 (Ain_19)
THERM21: J2.09, J5.A21 (Ain_20)
THERM22: J2.11, J5.B21 (Ain_21)
THERM23: J2.13, J5.A22 (Ain_22)
THERM24: J2.17, J5.B22 (Ain_23)
THERM25: J2.19, J5.A24 (Ain_24)
THERM26: J2.20, J5.B24 (Ain_25)
THERM27: J2.18, J5.A25 (Ain_26)
THERM28: J2.16, J5.B25 (Ain_27)
THERM29: J2.14, J5.A26 (Ain_28)
THERM30: J2.12, J5.B26 (Ain_29)
THERM31: J2.08, J5.A27 (Ain_30)
THERM32: J2.06, J5.B27 (Ain_31)
THERM33: J2.04, J5.A29 (Ain_32)
THERM34: J2.02, J5.B29 (Ain_33)
